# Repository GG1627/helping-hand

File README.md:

# Helping Hand - M5 Release Candidate

**Course:** CEN4908C  
**Project:** Helping Hand  
**Target milestone:** M5 Release Candidate
**Due:** October 28, 2026  
**Last updated:** October 28, 2026

Helping Hand is an American Sign Language (ASL) learning glove we are developing
for CEN4908C, Computer Engineering Senior Design. The glove measures finger bend
and wrist motion. An ESP32 processes the sensor readings and sends them over
Bluetooth Low Energy (BLE) to our Android Flutter app, where users can practice
signs, see live feedback, record gestures, and save their progress.

This repository contains our firmware, app, model-training code, hardware
documentation, and the KiCad files for our PCB design, which is still in progress.

- **Repository:** <https://github.com/GG1627/helping-hand>
- **Release candidate submission snapshot:** [`ff6a9ab`](https://github.com/GG1627/helping-hand/commit/ff6a9ab763f12f60e3a327d0df4f00a8784894b8)
- **Historical beta application snapshot:** [`d581d19`](https://github.com/GG1627/helping-hand/commit/d581d19)
- **Historical alpha validation commit:** [`cce9d38`](https://github.com/GG1627/helping-hand/commit/cce9d3887c5e52fafd4e35753f8e0de516051f79)
- **Android package:** `com.example.flutter_app`
- **Firebase project:** `helping-hand-83137`
- **Demo:** <https://www.youtube.com/shorts/qQmO1KYz998>
- **Team:** Brian, Gael, Kali, and Srinitha

**Current development handoff (November 6):** Software preparation for the
repaired glove is ready for physical calibration and real data collection. Start
with [the glove/model session handoff](docs/GLOVE_MODEL_SESSION_HANDOFF.md) for
completed changes, current model contracts, verification limits, and the next
steps once assembly is done. The milestone dates and historical evidence below
remain labeled for their original submissions.

## Milestone Overview

> The alpha results below are from commit `cce9d38`. Earlier beta work is
> documented in [`docs/BETA_BUILD_STATUS.md`](docs/BETA_BUILD_STATUS.md).
> The original assignments are in [`M4-Beta-Build.md`](M4-Beta-Build.md) and
> [`T2-Beta-Test-Plan.md`](T2-Beta-Test-Plan.md). Our beta work outline and test
> plan are available in [`output/pdf/M4_Beta_Build_Work_Outline.pdf`](output/pdf/M4_Beta_Build_Work_Outline.pdf)
> and [`output/pdf/T2_Beta_Test_Plan.pdf`](output/pdf/T2_Beta_Test_Plan.pdf).

Our alpha build connected the following parts of the system:

> Glove sensors → ESP32 static classifier → BLE packets → Flutter feedback
> → saved local progress → Firestore sync

As of October 27, about two of our flex sensors were broken, they were reading as flexed when they were not. We believe this is due to age. We ordered 5
Adafruit Short Flex Sensor #1070 replacements and an ICM-20948 nine-axis IMU
#4554. On November 5, Gael confirmed that all required parts have arrived,
including the replacement flex sensors, ICM-20948, and piezo elements. Sensor
replacement, installation, and calibration remain unconfirmed. Firmware support for the ICM-20948 and AK09916 magnetometer has now
been added, while keeping the older sensor path. The November 5 recording update
adds optional magnetic data to BLE and CSV/JSON exports as well as serial
diagnostics; see [the recording notes](docs/MAGNETOMETER_RECORDING.md).
The [ICM-20948 integration reference](research/ICM20948_INTEGRATION_REFERENCE.md)
covers wiring, calibration, fusion, current driver limitations, and recognition
experiments for the received nine-axis board.
Developer Mode now includes a [guided calibration workflow](docs/DEVELOPER_CALIBRATION.md)
for measured flex ranges, stationary gyro bias, axis checks, profile export,
and profile-linked raw recordings. Applying calibration to inference remains a
separate reviewed model/firmware update.
The [sequence preprocessing guide](docs/SEQUENCE_PREPROCESSING.md) documents
longer-window and 11/14-feature candidate preparation, strict no-trim checks,
and Python/Flutter parity. The deployed word model remains 96 × 11 until a
replacement is trained and validated.
Orientation fusion and new-board testing are still
pending. The BLE word-model inputs remain the existing six motion values. We have also received ten piezo buzzers: one for each finger and five
in an X on the back of the hand. The firmware now sets up all ten buzzer pins
and can play a timed PWM tone on one buzzer at a time without blocking the main
loop. We still need to review the circuit, decide how each cue should work,
and test it on the glove. The app and classifier do not trigger the buzzers yet.

Since the October 6 demo, we have continued working on the KiCad schematic,
planning the board layout, and looking into ways to improve the TCN. The PCB
layout is not finished, and we have not measured an improvement in model
accuracy from this work. More details are in the
[October 27 status notes](docs/R3_REPORT_READINESS.md).
We have also begun planning on how to sew in the flex sensors and the 9-axis IMU into the glove using conductive thread and have practiced making small circuits with conductive thread to get a feel for it before adding it to our project. We plan to use multiple layers of fabric (like a PCB) to ensure that we do not short any connections.

The app includes Record Signs and a trained TCN for Hello, Please, and Yes.
Users start an attempt, perform the sign, and finish the attempt. The phone
runs the model locally and saves completion when the prediction meets the
matching and confidence requirements. Recorded replay checks passed on the
Android emulator. Fresh glove testing is **Not run**. See the
[training notes](docs/WORD_MODEL_DEMO_TRAINING.md) and
[integration guide](docs/WORD_DEMO_INTEGRATION.md).

### Release Candidate Implementation
The RC keeps the full beta feature set and adds a custom PCB design:

1. Accounts: Firebase email/password account creation, sign-in, password reset, and sign-out.
- The app opens directly to sign-in/sign-up.
- An existing anonymous session is linked to the new account so its cloud progress is kept.

2. User-scoped progress:
- Local progress files and the Firestore document users/{uid}/progress/current are scoped to the signed-in Firebase user.
- Firebase Authentication stores credentials. Raw glove recordings stay in the CSV/JSON export workflow and are never uploaded to Firebase.

3. Static recognition: the recorded 34-class model is the default. The original 36-class (A–Z, 0–9) model is kept as a regression baseline, along with the stable-prediction completion rule.

4. Dynamic word recognition: TCN inference with saved completion for Hello, Please, and Yes.

5. Custom PCB (new in M5): KiCad schematic work and board-layout planning for the ESP32-S3 and 15 resistors in the flex-sensor and piezo circuits. The board is not yet routed or fabricated.
   
6. Process documentation:
- BETA_BUILD_PLAN.md

### Current Release Candidate Learning Flow
1. The app opens to login/signup. Login, signup, and Home use text-based Helping Hand branding, and the learning screens are styled to match.
2. Alphabet and Numbers are target pickers.
3.Words is an active vocabulary picker.
4. Tapping a letter, number, or word opens a separate live-practice page. Back returns to the picker. The pickers themselves contain no practice.
Letters and numbers: a target is completed when a matching prediction at ≥80% confidence stays stable for at least 750 ms and five packets. Progress is saved per account.
5. Hello, Please, Yes:
- Tap Start attempt, perform the whole sign, then tap Finish sign.
- Completion requires the predicted word to match the target at ≥80% confidence.
6. Other words: the pages remain available with recognition marked unavailable.
  
### M5 Work and Rubric Status

| Rubric category | What we have implemented | Testing and remaining work |
| --- | --- | --- |
| Usability: Interface | Account screens, branded Home and learning screens, Alphabet/Numbers/Words selection pages, and saved progress indicators. Each target has its own practice page. | Software layout checks were completed. Accessibility checks on the intended phone and usability testing with people outside the team are **Not run**. |
| Usability: Navigation | Users can select a target, open practice, return with Back, retry an attempt, and access account and connection controls. Other word pages explain when recognition is unavailable. | Current-phone navigation checks are **Not run**. A selected static target can still complete after leaving its practice page; we still need to decide how Back should handle an active target. |
| Usability: Perception | Static practice shows prediction, confidence, hold progress, Retry, and BLE connection status. Word practice shows the predicted word and attempt result. Account and save/sync status are also visible. | We still need to check whether users understand the feedback. Buzzer pins and timed tone control are set up, but automatic corrective cues and physical feedback tests are **Not run**. |
| Usability: Responsiveness | BLE and Firebase work asynchronously, Firebase starts when needed, and word inference runs in a background isolate. Buzzer timing is checked in the main loop without a blocking delay. | Latency on the intended phone and sustained BLE streaming measurements are **Not run**. |
| Build Quality: Robustness | We kept the original static model for regression checks. Word attempts check packet validity and timing and are canceled on disconnect, Back, or backgrounding. Progress is saved locally before cloud sync. | Earlier word integration passed 42 focused Flutter checks, three native Android recorded replay checks, and a debug APK build. Current repaired-glove regression, stress testing, and full account/offline tests are **Not run**. |
| Build Quality: Consistency | Static completion requires a matching prediction at 80% confidence or higher for at least 750 ms and five packets. Hello/Please/Yes use Start attempt / Finish sign and require the top predicted word to match at 80% confidence or higher. Progress is saved per account. | Repeatability across wearers and wrist angles, unrelated-motion rejection, and live account-isolation checks are **Not run**. The word model has no rest/unknown class. |
| Build Quality: Aesthetic Rigor | Login, signup, Home, and learning screens share the Helping Hand text branding, colors, and fonts. Practice pages use matching controls and feedback. We are also planning the PCB layout and how to sew the sensors into the glove. | Software visual/layout checks were completed. The PCB layout and sewn assembly are still in progress; final glove appearance, fit, and comfort tests are **Not run**. |

### Historical Beta Feature Status

| Area | What we added | Testing and remaining work |
| --- | --- | --- |
| Accounts | Firebase email/password signup, sign-in, password reset, and sign-out. Creating an account can link the existing anonymous account to keep its progress. | We reported signup and sign-in working, but did not record the exact build/device or complete all account tests. |
| Learning interface | Matching branding and colors, Alphabet/Numbers/Words selection pages, separate practice pages, and Back navigation. | Targeted code analysis and visual/software checks were completed. Current-phone navigation and usability tests with people outside the team are Not run. |
| Static recognition | A recorded 34-class MLP runs on the ESP32 by default. We kept the original synthetic 36-class model for comparison. | The recorded model excludes J/Z. Held-out recordings were evaluated for A, B, 1, and 3 only, so these results do not show accuracy across all classes or on fresh live attempts. See the [static model notes](docs/STATIC_MLP_DEMO_MODEL.md). |
| Word training | We compared TCN, CNN-GRU, and CNN-LSTM on 15 Hello/Please/Yes trials. Each model used the same nine training, three validation, and three test trials, with no trial split between sets. | All three models got 3/3 validation trials correct. TCN was selected because it was smallest and got 3/3 reserved test trials correct. The recordings came from one reported wearer at a neutral wrist angle, so we still need broader testing. |
| Word practice | The app runs the 48,324-byte TCN locally using Start attempt / Finish sign. Completion requires the top prediction to match the selected word at 80% confidence or higher. | 42 focused Flutter checks, three native Android recorded replay checks, and a debug APK build passed. Fresh glove recognition and latency on the intended phone are Not run. |
| Progress | Progress is saved locally for each user and synced to Firestore. Word completion uses the existing completed-exercise field. | We still need full app tests for word sync, restarting, switching accounts, offline recovery, and using another device. |
| Recording and preprocessing | Users can review complete trials, save or discard them, and export CSV/JSON files. Preprocessing resamples using device timestamps and fits standardization on training data only. | Raw recordings are stored separately from Firebase progress. We need more repetitions, wearers, and wrist angles. |
| Hardware feedback | We kept the existing flex/accelerometer/gyroscope BLE connection. Haptics were not integrated in the beta. | The later repair, IMU, buzzer, and PCB work is still in progress; ordering or receiving parts does not mean they have been integrated. |

### Historical Alpha Feature Status

| Area | Alpha status | Testing and limitations |
| --- | --- | --- |
| ESP32 sensor runtime | Implemented; September build passed | Reads five flex inputs and six accelerometer/gyroscope values and emits structured BLE packets. |
| Static sign classification | Implemented; tested on the earlier glove | The alpha build’s embedded 36-class TFLite MLP predicts `A`–`Z` and `0`–`9` from flex inputs. The team demonstrated glove-to-phone prediction and confidence output at the end of the previous semester. |
| BLE interface | Implemented; tested on the earlier glove | The app scans for `HelpingHand-Glove`, connects, subscribes to notifications, parses packets, and handles disconnect/reconnect states. Historical videos below show physical glove/sensor data reaching the phone. |
| Learner practice | Implemented; automated checks passed | A tile selects a target. Progress is awarded only after a matching prediction at or above 80% confidence remains stable for at least 750 ms and five packets. |
| Persistent progress | Implemented; automated checks passed | Learned letters, learned numbers, and completed exercises are saved locally first and synchronized to Firestore through anonymous authentication. |
| Record Signs | Implemented; pilot recording collected | The simplified static-sign flow selects a letter/number, counts down for three seconds, records live packets, and saves/exports CSV/JSON. A real-device pilot export is preserved in `backend/recorded_data/`; it is not model evidence because it has one signer and mostly one trial per label. |
| Word preprocessing | Implemented; automated checks passed | Schema validation, quality reports, fixed-rate resampling, fixed windows, deterministic splits, and train-only standardization are present. |
| Dynamic word models | Architecture foundation only | TCN, CNN-GRU, and CNN-LSTM candidates build and convert in software tests, but no real-data word training had been completed at that alpha snapshot. |
| Glove haptics | Research/design direction only | Research recommends beginning with small LRA actuators and a closed-loop driver. No haptic circuit, firmware command path, or physical validation existed at that alpha snapshot. |

### Historical Beta Rubric Traceability

| M4 requirement | What we implemented | What still needs testing or completion |
| --- | --- | --- |
| Usability, interface, and navigation | Matching account and learning screens, target selection, separate practice pages, Back, Retry, and progress indicators. | Current-phone control tests and usability sessions with people outside the team are Not run. |
| Perception | Connection status, predictions, confidence, hold progress, word results, and save/sync status are shown near the relevant controls. | We still need to check whether users understand the feedback. Haptics were not integrated in the beta. |
| Responsiveness | BLE and Firebase work asynchronously, and word inference runs in a background isolate. | Phone latency and sustained streaming measurements are Not run. |
| Robustness and consistency | A shared BLE service, stable static-match rules, word recording/cancellation checks, and software regression checks. | Hardware edge cases, stress tests, rejection of unrelated motion, and static completion after Back still need work or testing. |
| Aesthetic rigor | Consistent branding, bundled fonts, matching learning pages, and software layout checks. | On-device accessibility and glove appearance/comfort tests are Not run. |
| External interface | Account, practice, recording, and progress controls connect to the app services. | Word recognition supports Hello/Please/Yes only. Sign-specific instructional media and haptic feedback are incomplete. |
| Persistent state | Successful practice updates each user's local JSON progress and authenticated Firestore document. | We still need full tests for account separation, offline recovery, restoring progress after restart, and word sync. |
| Internal systems | The ESP32 runs static recognition, Flutter runs the TCN, and the backend handles sequence validation, training, and export. | More wearer/wrist-angle testing, calibration after repairs, and fresh glove-to-phone tests are pending. |
| Submission and effort evidence | Git history, training/integration notes, and beta work-outline/test-plan files record our work. | These files alone do not show that the M4 report, stakeholder defense, or every rubric requirement is complete. |

### Historical Alpha Rubric Traceability

| Alpha requirement | Helping Hand implementation |
| --- | --- |
| Usability and user control | Clearly labeled navigation, BLE scan/connect controls, learner target selection, retry/reset controls, and explicit recording save/discard/export actions. |
| Interface and navigation | Five persistent bottom-navigation destinations: Dashboard, Alphabet, Numbers, Record Signs, and BLE Testing. |
| Perception and feedback | Connection, prediction, confidence, hold progress, success/retry, recording quality, local-save, synchronization, offline, and failure states appear near the action they describe. |
| Responsiveness | BLE and Firebase work is asynchronous. Firebase initialization is lazy and cannot block application launch or local progress access. |
| Build quality and robustness | Flutter analysis, Flutter tests, Android APK build, ESP32 build, and the complete backend test suite pass on the validation environment documented below. |
| Vertical feature | The static learner loop connects physical sensor input, embedded inference, BLE transport, mobile feedback, and persistent learner state. |
| Persistent state | Progress is written to app-private local storage first and optionally synchronized to an authenticated, user-owned Firestore document. |
| Internal processing | The ESP32 performs static TFLite inference; Flutter validates stable predictions; the backend validates and prepares dynamic word sequences. |

### Architecture

```mermaid
flowchart LR
    FLEX[Five flex sensors] --> ESP[Adafruit Feather ESP32-S3]
    IMU[IMU accelerometer + gyroscope] --> ESP
    MODEL[Recorded 34-class static MLP] --> ESP
    ESP -->|BLE notifications| BLE[Flutter BLE service]
    BLE --> LIVE[Live telemetry and learner feedback]
    LIVE --> TRACKER[Stable-prediction validator]
    TRACKER --> PROGRESS[Progress repository]
    PROGRESS --> LOCAL[App-private local JSON]
    PROGRESS -->|Firebase email/password Auth| FIRESTORE[Cloud Firestore]
    BLE --> RECORD[Record Signs workflow]
    RECORD --> FILES[App-private CSV + JSON export]
    FILES --> BACKEND[Validation and sequence preprocessing]
    BACKEND --> WORDMODEL[Selected real-recording TCN]
    WORDMODEL --> WORDPRACTICE[Flutter complete word attempts]
    BLE --> WORDPRACTICE
    WORDPRACTICE --> PROGRESS
```

### Embedded Runtime

The firmware runs on the Adafruit Feather ESP32-S3 in
[`ESP32/src/main.cpp`](ESP32/src/main.cpp). It reads five flex sensors on
A0–A4 and communicates with the IMU over I2C (SDA=3, SCL=4).
[`imu_sensor.cpp`](ESP32/src/imu_sensor.cpp) now checks both 0x68 and 0x69 for
supported MPU-style parts or the new ICM-20948. The ICM path uses its own banked
register map, sets +/-2 g and +/-250 degrees/second ranges, and reads the
AK09916 magnetometer through I2C bypass. Compass data is checked for readiness
and overflow and reported in uncalibrated microteslas through serial diagnostics.
A read failure in the motion sensor marks it offline and enables discovery retries.
If the compass is unavailable, acceleration/gyro streaming can still continue.

BLE still sends the existing ax/ay/az in g and gx/gy/gz in degrees/second.
The current word model still uses five flex and six motion inputs; the new
magnetic readings do not change its input shape. Magnetic calibration,
axis alignment, fusion, and recognition on the replacement hardware still need
testing. The firmware changes are checked against the
[TDK datasheet](https://product.tdk.com/system/files/dam/doc/product/sensor/mortion-inertial/imu/data_sheet/ds-000189-icm-20948-v1.5.pdf).

The default static model is the recorded 34-class MLP; the original synthetic
36-class model is kept for regression checks. Firmware sends predictions and
confidence over BLE as `HelpingHand-Glove` and resumes advertising after a
disconnect. The configured stream rate is 40 Hz (adjustable to 25–50 Hz).
Phone-side rate and packet loss still need measurement.

The planned PCB schematic includes the ESP32-S3 and 15 resistors for the flex
and piezo circuits. Placement, routing, fabrication, and board testing are not
complete. The proposed sewn glove uses five fabric layers total: inner liner,
first routing fabric, insulating separator, second routing fabric, and outer
cover. This separates two routing levels; final routing and movement tests must
confirm whether more local insulation is needed. See
[`M5_Work_Outline.md`](M5_Work_Outline.md) for the assembly plan and references.

Host-side simulated-I2C regression checks passed; run
`python3 ESP32/test/imu_host_test.py` with Python 3 and `g++`.
The full build attempt timed out during installation of the missing
`tool-openocd-esp32` package, so board compilation is not confirmed. New IMU
bring-up, compass calibration, and sewn-glove testing are **Not run**.

The buzzers are outputs. [`piezo.cpp`](ESP32/src/piezo.cpp) sets all ten pins LOW
before waiting for the serial connection. `startPiezo(output, frequencyHz,
durationMs)` plays one tone at 50% duty cycle. `updatePiezos()` stops it from
the main loop when its time is up, and `stopPiezos()` cancels it early.

The code rejects requests before setup, while another buzzer is active, or with
an invalid output, frequency, or duration. It accepts 20–20,000 Hz and
1–5,000 ms; these are code limits, not confirmed ratings for our buzzers. One
LEDC channel is used for the selected pin, so only one buzzer can play at a
time. We still need to choose a frequency for the actual piezo and driver.
The buzzers stay off at startup and are not connected to app/classifier cues yet.

| Buzzer position | Feather pin label | ESP32-S3 GPIO |
| --- | --- | --- |
| Thumb | A5 | 8 |
| Index / pointer | D5 | 5 |
| Middle finger | D6 | 6 |
| Ring finger | D9 | 9 |
| Pinky | D10 | 10 |
| Hand matrix left | SCK | 36 |
| Hand matrix right | MISO | 37 |
| Hand matrix center | D12 | 12 |
| Hand matrix up | D11 | 11 |
| Hand matrix down | MOSI | 35 |

These pins come from the resistor names and board labels in
`pcb/pcb.kicad_sch`, checked against the Feather pin definitions. Left, right,
center, up, and down describe the buzzer positions; we have not tested them as
directional cues yet. SCK/MISO/MOSI are used as buzzer outputs here, so they
cannot also be used for SPI at the same time. Compile-time checks catch repeated
pins and conflicts with the flex or I2C pins. Physical buzzer output, how the
cues feel/sound, driver suitability, and timing while BLE is running are
**Not run**.

### Flutter Application
The Android Flutter app is in flutter_app/.

- Shared BLE service: owns scanning, connection, notification subscription, packet parsing, and reconnect behavior. Learner practice, Record Signs, and BLE Testing all consume the same packet stream.
- Authentication: Firebase email/password accounts gate entry to the app.
- Letter/number practice: tapping a target opens its practice page. Selecting a target does not mark it learned. The app requires a stable classifier match before saving completion, and shows the target, current prediction, confidence, connection state, hold progress, and success/retry messages.
- Word practice: the learner delimits each attempt with Start attempt / Finish sign. The TCN classifies the complete attempt locally on the phone.

### Local and Firebase Persistence
Progress uses a local-first repository design:

- The app loads the signed-in user's progress file from app-private application-support storage.
- Progress is written locally before cloud synchronization begins.
- Firebase initializes on demand rather than before runApp().
- Firebase email/password authentication provides the user identity. The alpha used anonymous authentication.
- The progress document syncs at users/{uid}/progress/current.
- Firestore rules allow an authenticated user to read and write only their own fixed progress document. Collection listing and document deletion are denied.
- If Firebase is unavailable, the app continues with its local copy and offers a retry action.

The document contains only:

schema version
learned letters
learned numbers
completed exercise identifiers
an update timestamp

Raw glove recordings are never uploaded to Firebase. The UI exposes loading, saved locally, syncing, synced, offline/local-only, and failure states. Malformed local state falls back to a safe empty representation rather than crashing.

### Word-Recording and ML Foundation
Record Signs creates labeled trials using the word-sequence-v1 contract.

- Word captures use Stop → review → Save trial / Discard trial.
- Each saved row keeps:
     - the exact BLE packet
     - parsed timestamps and sequence number
     - five flex readings and six IMU readings
     - label, pseudonymous signer ID, orientation, and trial metadata
- Sessions stay app-private until exported as CSV/JSON through the Android share sheet.

The backend can:

- validate columns, values, labels, metadata, sequence order, timestamps, rate, and sensor ranges;
- report malformed packets and gaps without repairing raw evidence;
- resample trials and create fixed-length windows;
- make deterministic splits that keep each trial and signer within one split;
- fit standardization on training data only;
- evaluate top-1 and top-5 accuracy, macro F1, confusion matrices, and signer/orientation groups;
- build and smoke-test TCN, CNN-GRU, and CNN-LSTM candidates with float TFLite conversion.

Synthetic fixtures are software-test data only and are marked non-reportable. The deployed TCN currently covers Hello, Please, and Yes. It was trained on recordings from a single wearer in a neutral orientation and has no rest/unknown class.

## Application Evidence

These updated screenshots show our sign-in and account screens, Home, learning
pages, and developer tools. Record Signs and BLE Testing show the disconnected
state. These images show the interface, not a new glove-recognition test.

<table>
  <tr>
    <td align="center"><br><strong>Sign in</strong></td>
    <td align="center"><br><strong>Create account</strong></td>
    <td align="center"><br><strong>Home</strong></td>
  </tr>
  <tr>
    <td align="center"><br><strong>Alphabet</strong></td>
    <td align="center"><br><strong>Numbers</strong></td>
    <td align="center"><br><strong>Words</strong></td>
  </tr>
  <tr>
    <td align="center"><br><strong>Record Signs</strong></td>
    <td align="center"><br><strong>BLE Testing</strong></td>
  </tr>
</table>

**Earlier app screenshots**

The screenshots below are from the earlier Android emulator build. The glove
was disconnected while we prepared the next hardware iteration. The Dashboard
shows the earlier app reaching its `Synced` progress-storage state.

<table>
  <tr>
    <td align="center"><br><strong>Start</strong></td>
    <td align="center"><br><strong>Dashboard and sync</strong></td>
    <td align="center"><br><strong>Alphabet practice</strong></td>
  </tr>
  <tr>
    <td align="center"><br><strong>Number practice</strong></td>
    <td align="center"><br><strong>Record Signs</strong></td>
    <td align="center"><br><strong>BLE Testing</strong></td>
  </tr>
</table>

### Glove Pictures

Our updated glove assembly is shown below. The photo documents the hardware
arrangement; the planned sewn assembly, nine-axis IMU integration, and ten-piezo
feedback system still need completion and testing.

### Historical Physical Integration Evidence

These short videos were recorded at the end of the previous development
semester. They establish that real flex-sensor changes reached the physical
Android phone over BLE and changed the live hand visualization. The team's
end-of-semester integration testing also displayed the static classifier's
predicted sign and confidence on the phone.

- [Bench flex sensor streaming to the phone (6 seconds)](app_glove_pictures_and_vids/vid-1.mp4)
- [Wearable glove connected to the phone (8 seconds)](app_glove_pictures_and_vids/vid-2.mp4)

The videos are historical validation of the glove/BLE baseline. The current
Firebase persistence, stable-prediction completion logic, and Record Signs
workflow were validated through the current automated tests and emulator build;
they were not present in exactly this form in the historical video.

## Release Candidate Navigation and Use

### 1. Start and Dashboard

1. Launch the app and create an account or sign in with email and password.
2. Home loads the signed-in user's local progress copy.
3. The Progress storage card reports whether data is loading, saved locally,
   syncing, synced, offline, or failed.
4. **Retry sync** appears when remote synchronization is unavailable.
5. **Reset progress** requires confirmation before clearing progress locally
   and synchronizing the empty state.

### 2. Connect the glove

1. Power the flashed ESP32 glove.
2. Enable Bluetooth and grant the Android permissions requested by the app.
3. Open **Developer Mode > BLE Testing** and select **Start Scan**, or select **Find glove** from
   Record Signs.
4. The app targets the advertised name `HelpingHand-Glove` and can auto-connect
   when it appears.
5. A connected status and incoming values indicate a successful notification
   subscription.

### 3. Complete a learner item

1. Open **Alphabet** or **Numbers**.
2. Select one target tile to open its practice page. The current default
   recorded static model supports 0–9 and letters except J/Z.
3. Form the matching static sign with the connected glove.
4. Hold the matching prediction at 80% confidence or higher for at least
   750 ms and five packets.
5. The interface displays hold progress, `correct`, `try again`, low-confidence,
   and disconnected states near the exercise.
6. After success, the item is marked learned and saved through the progress
   repository.

### 4. Record a word trial

To practice an already trained word, open Words > Hello, Please, or Yes, tap
Start attempt, perform the complete sign, then Finish sign. A matching result
at 80% confidence or above saves completion. See
[the word demo guide](docs/WORD_DEMO_INTEGRATION.md) for timing and rehearsal.
The steps below collect additional training recordings.

1. Open **Record Signs** and connect the glove.
2. Enter a lowercase word label, vocabulary version, pseudonymous signer ID,
   orientation condition, and unique trial ID.
3. Wait for a complete, fresh packet and select **Start recording**.
4. Perform one complete gesture, then stop and review duration, packet count,
   delivered rate, valid packets, and warnings.
5. Save a clean trial or discard it with a reason.
6. Export the selected session's CSV and JSON through the share sheet.

Use pseudonymous IDs such as `signer_01`. Never enter a participant's name or
email address, upload raw recordings to Firebase, or commit participant
recordings to Git.

## Prerequisites

The documented alpha validation environment on Windows used:

- Git;
- Flutter `3.41.6` stable and Dart `3.11.4`;
- Android Studio/Android SDK and an Android emulator or physical Android phone;
- a Java installation supported by the installed Flutter/Android toolchain;
- Python `3.10.11` for the complete TensorFlow backend suite;
- TensorFlow `2.21.0` and pytest `9.1.1`; and
- PlatformIO Core `6.1.19`.

A physical Android device is required for meaningful BLE validation. An
emulator can validate navigation, local persistence, and Firebase behavior but
does not represent real glove discovery or sensor streaming.

## Clone the repository

```powershell
git clone https://github.com/GG1627/helping-hand.git
cd helping-hand
```

If the repository is private, the project owner must grant the instructors
access before submission.

## Build and run the Flutter app

```powershell
cd flutter_app
flutter pub get
flutter analyze
flutter test
flutter build apk --debug
flutter devices
flutter run -d <android-device-id>
```

The debug APK is generated at:

```text
flutter_app/build/app/outputs/flutter-apk/app-debug.apk
```

The Android Firebase client configuration targets the project listed above.
Running the app does not require a service-account key. Use a team-provided
test account; do not put credentials in this repository. The current application
provides email/password account creation and sign-in. The older alpha used
anonymous authentication; that historical behavior is not the current account
flow.

For project maintainers only, Firestore rules are defined in
[`flutter_app/firestore.rules`](flutter_app/firestore.rules). Always verify the
selected Firebase project before deployment:

```powershell
cd flutter_app
npx firebase-tools use helping-hand-83137
npx firebase-tools use
npx firebase-tools deploy --only firestore --project helping-hand-83137
```

Do not deploy open/test-mode rules, create service-account keys for the mobile
app, or select any unrelated Firebase project.

## Build, upload, and monitor the ESP32 firmware

Install PlatformIO if it is not already available:

```powershell
py -3.10 -m pip install platformio
```

Build the firmware:

```powershell
cd ESP32
platformio run
```

Connect the Feather ESP32-S3, identify its serial port, then upload and monitor:

```powershell
platformio run --target upload --upload-port <COM-port>
platformio device monitor --baud 115200 --port <COM-port>
```

Expected output includes BLE advertising status and telemetry beginning with
`seq=...`, `t_ms=...`, and sensor fields. Hard-coded ML test mode is disabled in
the submitted source; normal packets use live flex readings.

The target recording rate can be changed at compile time to an integer from 25
through 50 Hz with `HH_SENSOR_RATE_HZ`. The default is 40 Hz.

## Set up and test the backend

Create a clean Python 3.10 environment from the repository root:

```powershell
py -3.10 -m venv .venv
.\.venv\Scripts\python.exe -m pip install --upgrade pip
.\.venv\Scripts\python.exe -m pip install -r requirements.txt
.\.venv\Scripts\python.exe -m pytest backend/tests -q
```

Validate a real exported Record Signs session without editing it:

```powershell
.\.venv\Scripts\python.exe backend/prepare_word_sequences.py path/to/trials.csv
```

The model-development entry points support further training and evaluation.
The three-word demo is already trained; broader recognition requires more
real recordings and an evaluation protocol appropriate to the expanded scope:

```powershell
.\.venv\Scripts\python.exe backend/train_word_models.py --help
.\.venv\Scripts\python.exe backend/evaluate_word_models.py --help
```

See [`backend/data/README.md`](backend/data/README.md) for the schema and
privacy contract and [`backend/models/README.md`](backend/models/README.md) for
the model artifact policy.
Optional training-only perturbations for static and word candidates are documented
in [training augmentation](docs/TRAINING_AUGMENTATION.md). They default to disabled
until the repaired glove supplies measured limits.

## BLE packet contract

The firmware and app share Nordic UART-style service and characteristic UUIDs.
Each complete notification contains a monotonically increasing sequence ID,
device uptime, IMU identity, six motion values, static prediction and
confidence, and five raw/normalized flex readings:

```text
seq=...,t_ms=...,who=0xNN,
ax=...,ay=...,az=...,gx=...,gy=...,gz=...,
expected=...,pred=...,pred_conf=...,
flex0_raw=...,flex0_norm=...,...,flex4_raw=...,flex4_norm=...
```

Malformed notifications are retained by the recording path with their original
packet text and are marked invalid rather than silently repaired.

## Historical Alpha Validation Results

These commands were run on **September 10, 2026** against implementation commit
`cce9d3887c5e52fafd4e35753f8e0de516051f79`:

| Validation | Result |
| --- | --- |
| `flutter analyze` | Passed — no issues found |
| `flutter test` | Passed — all 16 tests |
| `flutter build apk --debug` | Passed — debug APK produced |
| `platformio run` in `ESP32/` | Passed for `adafruit_feather_esp32s3` |
| ESP32 memory report | 37.6% RAM and 83.9% of configured application flash |
| Complete `pytest backend/tests -q` with TensorFlow installed | Passed — 23 tests; 3 non-failing TFLite interpreter deprecation warnings |
| Firebase environment | Correct alpha project verified; Anonymous Authentication enabled; Firestore available |
| Firestore rules | Deployed and read back; authenticated owner-only fixed progress document; no open/test-mode access |
| Historical alpha emulator run | Dashboard reached `Synced` in the September evidence |
| Historical physical run | Glove/flex data reached a physical Android phone over BLE and changed the live visualization; static predictions and confidence were demonstrated by the team |

These results show what passed on the September build. We still need to test
the current software on the repaired glove. The older videos show the earlier
glove-to-phone connection; that glove was unavailable for another test when
the screenshots were taken.

## Repository layout

| Path | Purpose |
| --- | --- |
| [`ESP32/`](ESP32/) | Feather ESP32-S3 firmware, static model header, and IMU diagnostics |
| [`flutter_app/`](flutter_app/) | Android Flutter application, BLE client, learner loop, recording, local persistence, Firebase sync, and tests |
| [`pcb/`](pcb/) | In-progress KiCad schematic and board-design files for the planned glove PCB. |
| [`backend/`](backend/) | Static artifacts, word-sequence validation/preprocessing, candidate training/selection/export, and tests |
| [`docs/`](docs/) | Word-data collection and project documentation |
| [`research/`](research/) | Word-level IMU recognition and haptic-feedback research |
| [`app_glove_pictures_and_vids/`](app_glove_pictures_and_vids/) | Earlier emulator screenshots and historical physical integration evidence |
| [`hardware_pictures/`](hardware_pictures/) | Assembly and soldering photographs |
| [`design_draft/`](design_draft/) | Original design document, Figma concepts, storyboard, networking diagram, and legacy schematic draft |
| [`PLAN.md`](PLAN.md) | Living dynamic-word implementation plan |
| [`ALPHA_BUILD_PLAN.md`](ALPHA_BUILD_PLAN.md) | Deadline-oriented alpha planning and acceptance checklist |
| [`BETA_BUILD_PLAN.md`](BETA_BUILD_PLAN.md) | Beta implementation summary, architecture, historical evidence, and known limitations |

### Hardware documentation note

The schematic in `design_draft/schematic/` is our original ESP32-C3/LSM9DS1
concept, so it does not show the Feather ESP32-S3 glove wiring. Refer to the
firmware pin definitions and hardware photos for the alpha setup. Our current
KiCad schematic is
[`pcb/pcb.kicad_sch`](pcb/pcb.kicad_sch), with board-design files under `pcb/`.

## Known Bugs and Incomplete Release Candidate Features

1. ESP32 firmware startup - The November 6 update bounds the optional USB Serial
   wait to approximately 1.5 seconds before continuing to sensor/BLE setup.
   Firmware compilation and host checks passed; physical battery-only boot is
   Not run. See [startup and demo evaluation tools](docs/DEMO_READINESS_TOOLS.md).

2. Flutter practice lifecycle -	A selected letter or number stays active after leaving its practice page. The app shell keeps accepting matching packets and can record completion while the learner is on the picker.

3. Issues with the BLE connection + Power.

4. The flex sensors are bent so the readings are off meaning the ML prediction is incorrect - Purchased new sensors.

## AI-Assisted Development Disclosure
We used approved generative AI tools to help with parts of the research,
planning, code, testing, and documentation, following the
[course AI-use policy](ai-policy/AI-USAGE.md). AI-assisted commits include
`GENAI=Yes` in the subject and an `AI-Assisted` trailer. Our team is responsible
for reviewing, understanding, testing, and presenting the submitted work.

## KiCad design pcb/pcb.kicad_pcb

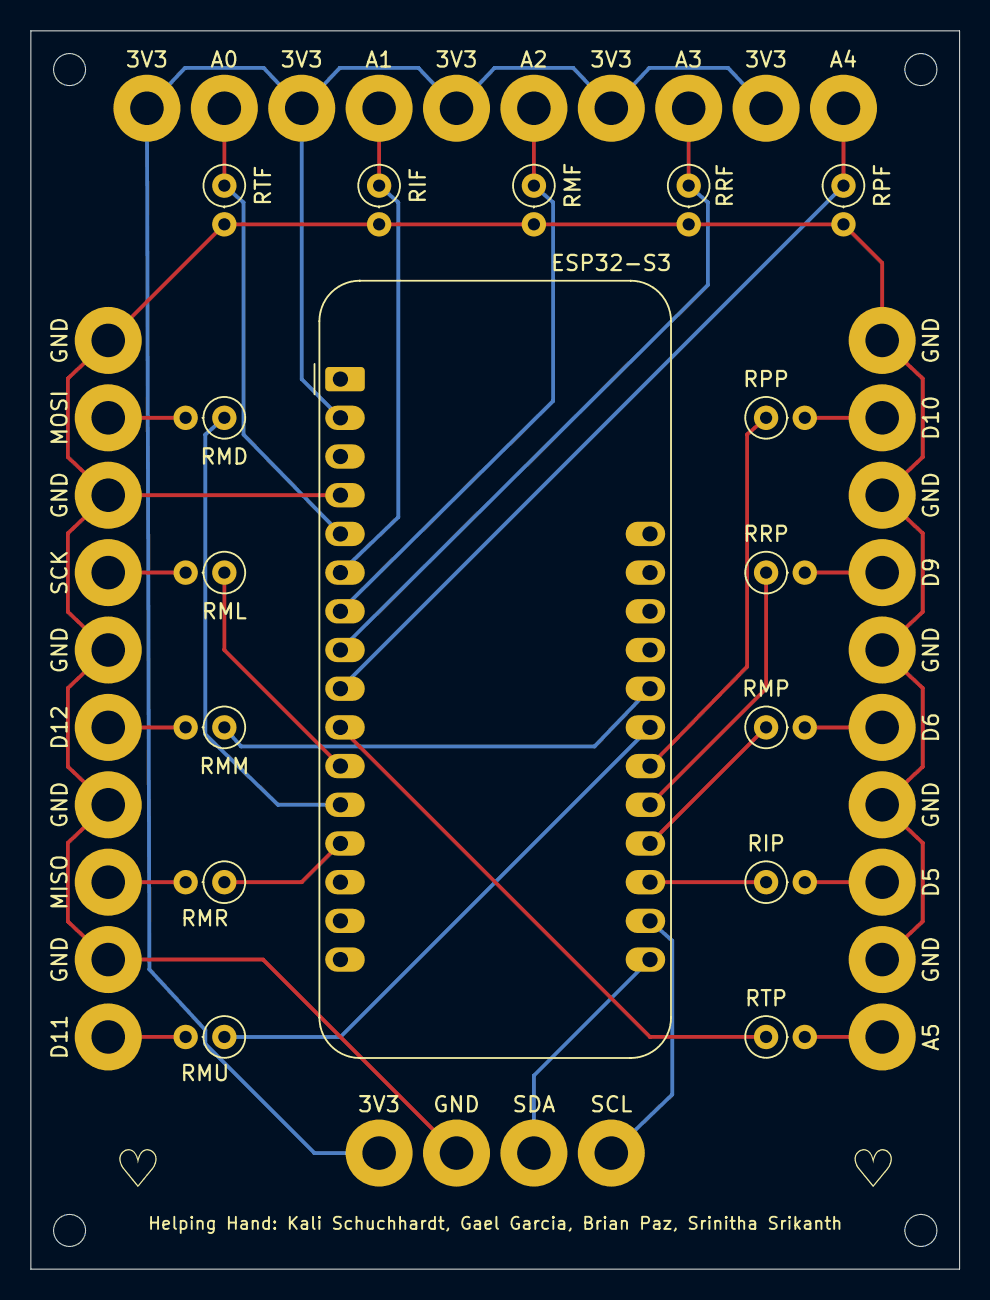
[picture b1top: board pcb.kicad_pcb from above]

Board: 2 copper layers, 61.0 x 81.3 mm, 50 parts (0 on the bottom side), 29 nets.

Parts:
3V3, 3V3#2, 3V3#3, 3V3#4, 3V3#5, 3V3#6: MountingHole_2.2mm_M2_Pad
A0, A1, A2, A3, A4, A5: MountingHole_2.2mm_M2_Pad
D5, D6, D9, D10, D11, D12: MountingHole_2.2mm_M2_Pad
ESP32-S3: Adafruit_Feather_Generic; Adafruit_Feather
GND: MountingHole_2.2mm_M2_Pad
GND#2, GND#3, GND#4, GND#5, GND#6, GND#7, GND#8, GND#9, GND#10, GND#11: MountingHole_2.2mm_M2_Pad
MISO: MountingHole_2.2mm_M2_Pad
MOSI: MountingHole_2.2mm_M2_Pad
RIF: 47k; R_Axial_DIN0207_L6.3mm_D2.5mm_P2.54mm_Vertical
RIP: 1k; R_Axial_DIN0207_L6.3mm_D2.5mm_P2.54mm_Vertical
RMD: 1k; R_Axial_DIN0207_L6.3mm_D2.5mm_P2.54mm_Vertical
RMF: 47k; R_Axial_DIN0207_L6.3mm_D2.5mm_P2.54mm_Vertical
RML: 1k; R_Axial_DIN0207_L6.3mm_D2.5mm_P2.54mm_Vertical
RMM: 1k; R_Axial_DIN0207_L6.3mm_D2.5mm_P2.54mm_Vertical
RMP: 1k; R_Axial_DIN0207_L6.3mm_D2.5mm_P2.54mm_Vertical
RMR: 1k; R_Axial_DIN0207_L6.3mm_D2.5mm_P2.54mm_Vertical
RMU: 1k; R_Axial_DIN0207_L6.3mm_D2.5mm_P2.54mm_Vertical
RPF: 47k; R_Axial_DIN0207_L6.3mm_D2.5mm_P2.54mm_Vertical
RPP: 1k; R_Axial_DIN0207_L6.3mm_D2.5mm_P2.54mm_Vertical
RRF: 47k; R_Axial_DIN0207_L6.3mm_D2.5mm_P2.54mm_Vertical
RRP: 1k; R_Axial_DIN0207_L6.3mm_D2.5mm_P2.54mm_Vertical
RTF: 47k; R_Axial_DIN0207_L6.3mm_D2.5mm_P2.54mm_Vertical
RTP: 1k; R_Axial_DIN0207_L6.3mm_D2.5mm_P2.54mm_Vertical
SCK: MountingHole_2.2mm_M2_Pad
SCL: MountingHole_2.2mm_M2_Pad
SDA: MountingHole_2.2mm_M2_Pad

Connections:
/3.3V: 3V3.1, 3V3#2.1, 3V3#3.1, 3V3#4.1, 3V3#5.1, 3V3#6.1, ESP32-S3.2 (3V3)
/A0: A0.1, ESP32-S3.5 (A0), RTF.1
/A1: A1.1, ESP32-S3.6 (A1), RIF.1
/A2: A2.1, ESP32-S3.7 (A2), RMF.1
/A3: A3.1, ESP32-S3.8 (A3), RRF.1
/A4: A4.1, ESP32-S3.9 (A4), RPF.1
/A5: ESP32-S3.10 (A5), RTP.1
/D5: ESP32-S3.19 (D0), RIP.1
/D6: ESP32-S3.20 (D1), RMP.1
/D9: ESP32-S3.21 (D2), RRP.1
/D10: ESP32-S3.22 (D3), RPP.1
/D11: ESP32-S3.23 (D4), RMU.1
/D12: ESP32-S3.24 (D5), RMM.1
/MISO: ESP32-S3.13 (MISO), RMR.1
/MOSI: ESP32-S3.12 (MOSI), RMD.1
/SCK: ESP32-S3.11 (SCK), RML.1
/SCL: ESP32-S3.18 (SCL), SCL.1
/SDA: ESP32-S3.17 (SDA), SDA.1
GND: ESP32-S3.4 (GND), GND.1, GND#2.1, GND#3.1, GND#4.1, GND#5.1, GND#6.1, GND#7.1, GND#8.1, GND#9.1, GND#10.1, GND#11.1, RIF.2, RMF.2, RPF.2, RRF.2, RTF.2
a5_piezo_input: A5.1, RTP.2
d5_piezo_input: D5.1, RIP.2
d6_piezo_input: D6.1, RMP.2
d9_piezo_input: D9.1, RRP.2
d10_piezo_input: D10.1, RPP.2
d11_piezo_input: D11.1, RMU.2
d12_piezo_input: D12.1, RMM.2
miso_piezo_input: MISO.1, RMR.2
mosi_piezo_input: MOSI.1, RMD.2
sck_piezo_input: RML.2, SCK.1

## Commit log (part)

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2026-03-11 adding figma mockup screen for mobile app
2026-03-12 added rest of design draft files and cleaned up repo
2026-03-20 added basic project setup and started ml model - created synthetic data
2026-03-20 adding root files - forgot to add whoops
2026-03-20 trained MLP model for asl classification
2026-03-20 added front end folder
2026-03-20 update READNE, remove react native app reference
2026-03-24 Fix spacing
2026-03-24 Include Flutter BLE documentation
2026-03-31 set up flutter app - very basic for now
2026-03-31 Add initial ESP32 BLE firmware
    I practiced Bluetooth Low Energy using NimBLE for better memory efficiency, as well as set up example Service and Characteristic UUIDs for the glove.
2026-03-31 Rename main.cpp to main.ino
2026-04-03 updated structure of the flutter app
2026-04-03 solder (before)
    soldering the esp32
2026-04-03 Rename Screenshot 2026-04-03 143821.png to SolderBeforeESP32
2026-04-03 Rename SolderBeforeESP32 to SolderBeforeESP32.png
2026-04-03 Solder (after)
    Soldering the pins on the ESP32
2026-04-03 updated the styling and theme of flutter app and made it more modular
2026-04-03 Rename Screenshot 2026-04-03 160637.png to SolderAfterESP32.png
2026-04-03 added BLE to app and research coin motors
2026-04-03 Add dynamic letter and number tracking with overall progress
2026-04-03 added platformio folder for esp32 stuff
2026-04-03 pushing for testing
2026-04-03 Changed ESP32 Board Config
2026-04-03 BLE is workingggggggg
2026-04-05 update gitignore
2026-04-05 added MPU datasheet/documents
2026-04-05 spent 5 hours trying to connect MPU, i think its dead, doesnt work
2026-04-06 ~2 more hours working and finally got MPU working, added documentation of full testing we did to get it working
2026-04-06 added ESP32 ble sending data - have to check it with nrfConnect, emulators cannot get ble :(
2026-04-06 updated README for prealphabuild
2026-04-06 Add meeting logs for March and April 2026
2026-04-06 Adjust formatting
2026-04-06 Add contributions tracking section
2026-04-06 Finalizing pre-alpha UI and shell updates
2026-04-07 Added one flex sensor and link that i used to help wire it up - added data to be sent over BLE
2026-04-07 Added other 4 flex sensors
2026-04-07 Changing structure...
2026-04-09 added polygon hand into app for presentation demo purposes
2026-04-09 soldered jumper cables to flex sensors
2026-04-09 updated ml model to be trained on values that we actually get from our flex sensors, values range from ~150-~550
2026-04-09 added ml prediction/inference to esp, now runs on the model - yay
2026-04-09 Add meeting log for 04/09/26
2026-04-09 Add meeting log for 04/07/26
2026-04-10 got ble working on physical andriod phone, it can now scan and see other devices
2026-04-10 updated demo hand to use live flex sensor values and show bending etc - added video of proof
2026-04-10 updated UI to be more responsive and fix weird uneven spacing
2026-04-10 added IMU hand rotation using real live data, for demo purposes
2026-04-13 firebase connection
2026-04-14 Add documentation for Srinitha's contributions
    Document Srinitha's contributions on project.
2026-04-14 remove key
2026-04-14 remove remaining keys
